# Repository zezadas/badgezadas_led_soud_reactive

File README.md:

# badgezadas_led_soud_reactive

Example of an analog badge which reacts to sound and blinks some leds. It also includes an IV led that can be used on a CTF, using invisible ink.

Design is very simple. It is recommended to adapt once forked.

TODO:

 - better readme

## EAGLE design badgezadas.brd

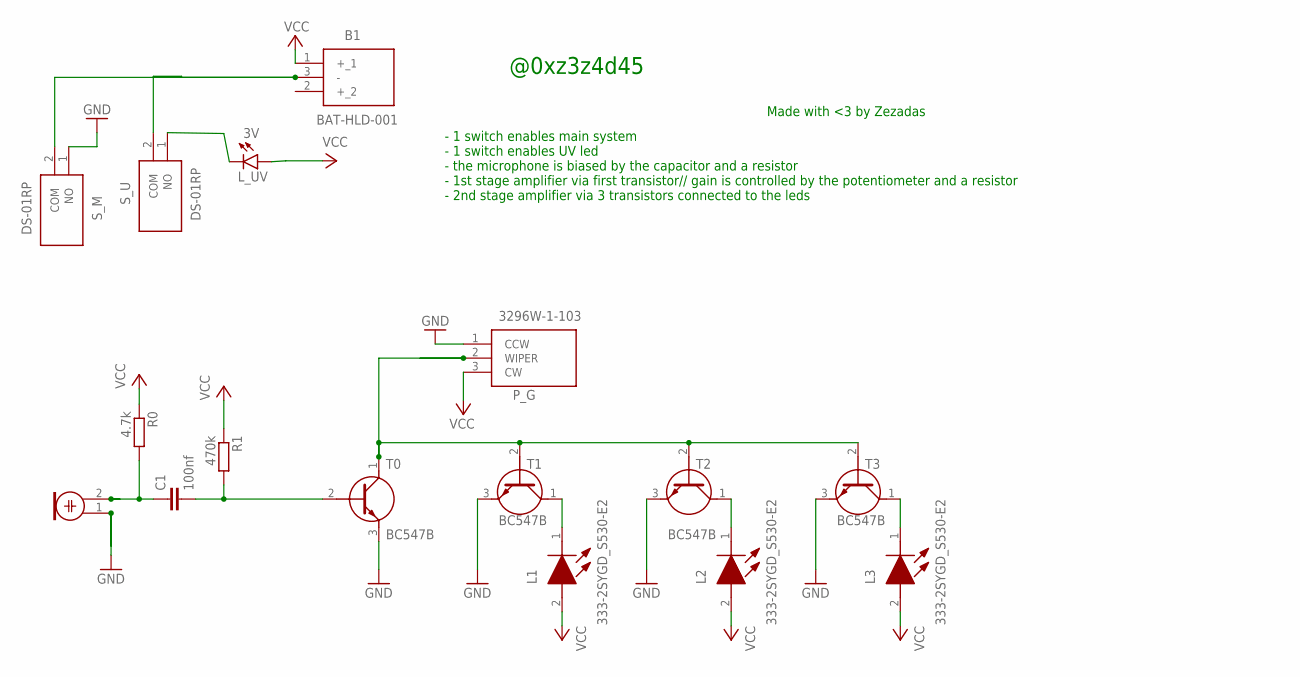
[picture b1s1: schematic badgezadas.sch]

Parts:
B1: BAT-HLD-001; BATHLD001
C1: 100nf; C025-024X044
L1, L2, L3: 333-2SYGD_S530-E2; 3332SYGDS530E2
L_UV: 3V; LED3MM
M0: ELECTRET_MICROPHON-F6050AP; F6050AP
P_G: 3296W-1-103; 3296W1103
R0: 4.7k; 0207/10
R1: 470k; 0207/10
S_M: DS-01RP; DS01RP
S_U: DS-01RP; DS01RP
T0, T1, T2, T3: BC547B; TO-92-PLASTIC_2

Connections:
GND: M0.1, P_G.1 (CCW), S_M.1 (NO), T0.3 (E), T1.3 (E), T2.3 (E), T3.3 (E)
unnamed: C1.1, M0.2, R0.2
unnamed: C1.2, R1.2, T0.2 (B)
unnamed: L_UV.K (C), S_U.1 (NO)
unnamed: P_G.2 (WIPER), T0.1 (C), T1.2 (B), T2.2 (B), T3.2 (B)
unnamed: L1.1 (K), T1.1 (C)
unnamed: L3.1 (K), T3.1 (C)
unnamed: B1.3 (-), S_M.2 (COM), S_U.2 (COM)
unnamed: L2.1 (K), T2.1 (C)
VCC: B1.1 (+_1), L1.2 (A), L2.2 (A), L3.2 (A), L_UV.A, P_G.3 (CW), R0.1, R1.1

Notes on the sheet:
- 1 switch enables main system - 1 switch enables UV led - the microphone is biased by the capacitor and a resistor - 1st stage amplifier via first transistor// gain is controlled by the potentiometer and a resistor - 2nd stage amplifier via 3 transistors connected to the leds
Made with <3 by Zezadas
@0xz3z4d45

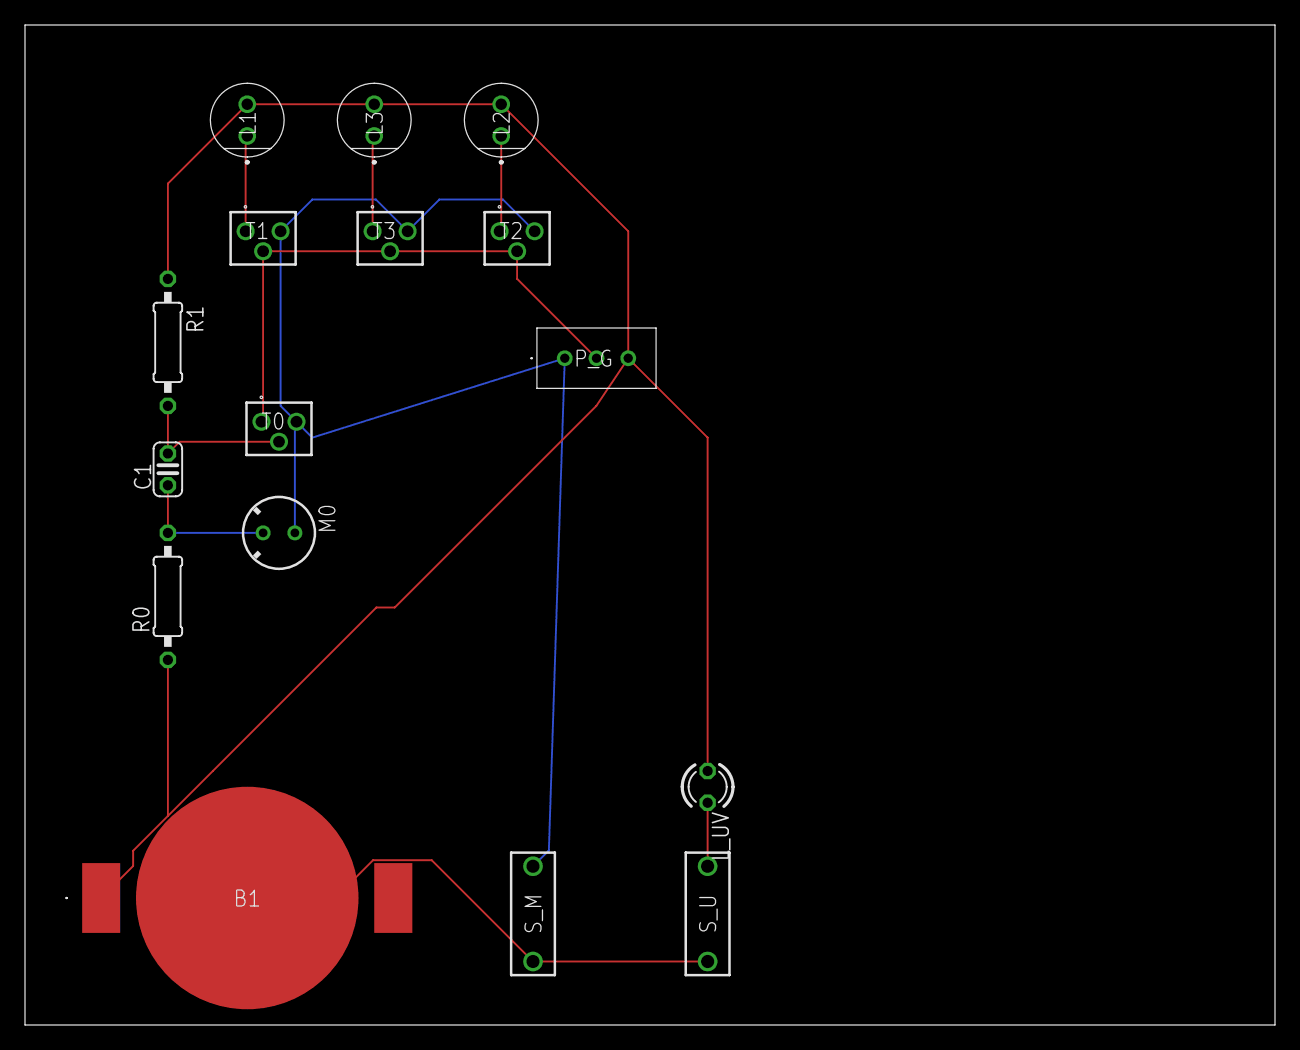
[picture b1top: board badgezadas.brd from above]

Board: 2 copper layers, 100.0 x 80.0 mm, 16 parts (0 on the bottom side), 10 nets.
